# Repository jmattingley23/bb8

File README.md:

# bb8
full size sci-fi ball robot

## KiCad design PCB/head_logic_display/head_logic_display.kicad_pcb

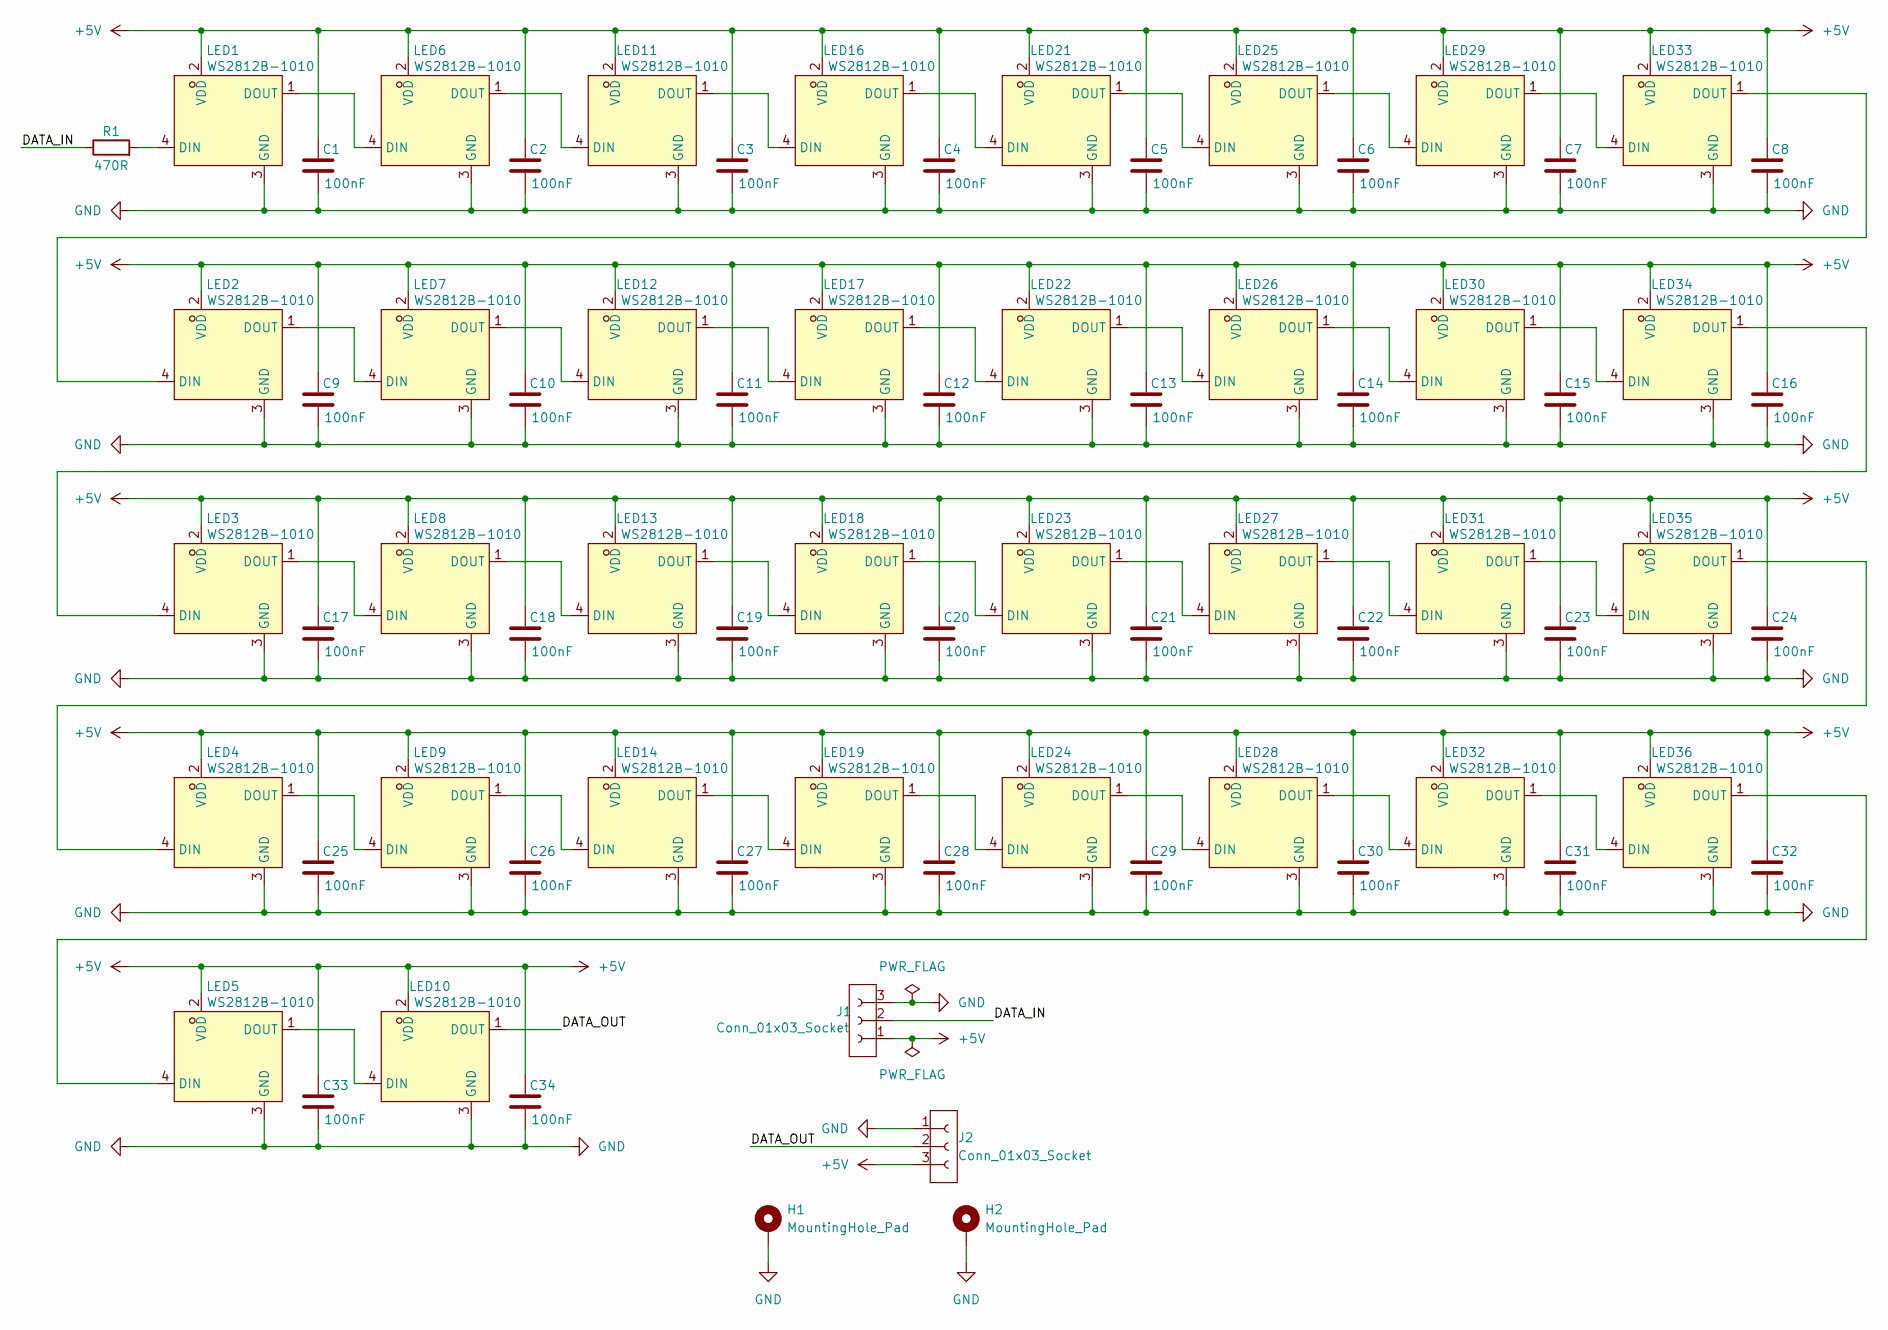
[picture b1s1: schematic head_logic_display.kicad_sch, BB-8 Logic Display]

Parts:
C1, C2, C3, C4, C5, C6, C7, C8, C9, C10, C11, C12, C13, C14, C15, C16, C17, C18, C19, C20, C21, C22, C23, C24, C25, C26, C27, C28, C29, C30, C31, C32, C33, C34: 100nF; C_0402_1005Metric; LCSC Part C307331
H1, H2: MountingHole_Pad; MountingHole_2.5mm_Pad_Via
J1, J2: Conn_01x03_Socket; JST_XH_S3B-XH-A-1_1x03_P2.50mm_Horizontal
LED1, LED2, LED3, LED4, LED5, LED6, LED7, LED8, LED9, LED10, LED11, LED12, LED13, LED14, LED16, LED17, LED18, LED19, LED21, LED22, LED23, LED24, LED25, LED26, LED27, LED28, LED29, LED30, LED31, LED32, LED33, LED34, LED35, LED36: WS2812B-1010; LED-SMD_4P-L1.0-W1.0-TL_XL-1010RGBC-WS2812B; LCSC Part C5349953
R1: 470R; R_0603_1608Metric; LCSC Part C23182

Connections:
+5V: C1.1, C2.1, C3.1, C4.1, C5.1, C6.1, C7.1, C8.1, C9.1, C10.1, C11.1, C12.1, C13.1, C14.1, C15.1, C16.1, C17.1, C18.1, C19.1, C20.1, C21.1, C22.1, C23.1, C24.1, C25.1, C26.1, C27.1, C28.1, C29.1, C30.1, C31.1, C32.1, C33.1, C34.1, J1.1, J2.3, LED1.2 (VDD), LED2.2 (VDD), LED3.2 (VDD), LED4.2 (VDD), LED5.2 (VDD), LED6.2 (VDD), LED7.2 (VDD), LED8.2 (VDD), LED9.2 (VDD), LED10.2 (VDD), LED11.2 (VDD), LED12.2 (VDD), LED13.2 (VDD), LED14.2 (VDD), LED16.2 (VDD), LED17.2 (VDD), LED18.2 (VDD), LED19.2 (VDD), LED21.2 (VDD), LED22.2 (VDD), LED23.2 (VDD), LED24.2 (VDD), LED25.2 (VDD), LED26.2 (VDD), LED27.2 (VDD), LED28.2 (VDD), LED29.2 (VDD), LED30.2 (VDD), LED31.2 (VDD), LED32.2 (VDD), LED33.2 (VDD), LED34.2 (VDD), LED35.2 (VDD), LED36.2 (VDD)
/DATA_IN: J1.2, R1.1
/DATA_OUT: J2.2, LED10.1 (DOUT)
GND: C1.2, C2.2, C3.2, C4.2, C5.2, C6.2, C7.2, C8.2, C9.2, C10.2, C11.2, C12.2, C13.2, C14.2, C15.2, C16.2, C17.2, C18.2, C19.2, C20.2, C21.2, C22.2, C23.2, C24.2, C25.2, C26.2, C27.2, C28.2, C29.2, C30.2, C31.2, C32.2, C33.2, C34.2, H1.1, H2.1, J1.3, J2.1, LED1.3 (GND), LED2.3 (GND), LED3.3 (GND), LED4.3 (GND), LED5.3 (GND), LED6.3 (GND), LED7.3 (GND), LED8.3 (GND), LED9.3 (GND), LED10.3 (GND), LED11.3 (GND), LED12.3 (GND), LED13.3 (GND), LED14.3 (GND), LED16.3 (GND), LED17.3 (GND), LED18.3 (GND), LED19.3 (GND), LED21.3 (GND), LED22.3 (GND), LED23.3 (GND), LED24.3 (GND), LED25.3 (GND), LED26.3 (GND), LED27.3 (GND), LED28.3 (GND), LED29.3 (GND), LED30.3 (GND), LED31.3 (GND), LED32.3 (GND), LED33.3 (GND), LED34.3 (GND), LED35.3 (GND), LED36.3 (GND)
unnamed: LED1.4 (DIN), R1.2
unnamed: LED1.1 (DOUT), LED6.4 (DIN)
unnamed: LED2.4 (DIN), LED33.1 (DOUT)
unnamed: LED2.1 (DOUT), LED7.4 (DIN)
unnamed: LED3.4 (DIN), LED34.1 (DOUT)
unnamed: LED3.1 (DOUT), LED8.4 (DIN)
unnamed: LED4.1 (DOUT), LED9.4 (DIN)
unnamed: LED5.1 (DOUT), LED10.4 (DIN)
unnamed: LED6.1 (DOUT), LED11.4 (DIN)
unnamed: LED11.1 (DOUT), LED16.4 (DIN)
unnamed: LED7.1 (DOUT), LED12.4 (DIN)
unnamed: LED12.1 (DOUT), LED17.4 (DIN)
unnamed: LED8.1 (DOUT), LED13.4 (DIN)
unnamed: LED13.1 (DOUT), LED18.4 (DIN)
unnamed: LED9.1 (DOUT), LED14.4 (DIN)
unnamed: LED14.1 (DOUT), LED19.4 (DIN)
unnamed: LED16.1 (DOUT), LED21.4 (DIN)
unnamed: LED17.1 (DOUT), LED22.4 (DIN)
unnamed: LED18.1 (DOUT), LED23.4 (DIN)
unnamed: LED19.1 (DOUT), LED24.4 (DIN)
unnamed: LED21.1 (DOUT), LED25.4 (DIN)
unnamed: LED22.1 (DOUT), LED26.4 (DIN)
unnamed: LED23.1 (DOUT), LED27.4 (DIN)
unnamed: LED24.1 (DOUT), LED28.4 (DIN)
unnamed: LED25.1 (DOUT), LED29.4 (DIN)
unnamed: LED26.1 (DOUT), LED30.4 (DIN)
unnamed: LED27.1 (DOUT), LED31.4 (DIN)
unnamed: LED28.1 (DOUT), LED32.4 (DIN)
unnamed: LED29.1 (DOUT), LED33.4 (DIN)
unnamed: LED30.1 (DOUT), LED34.4 (DIN)
unnamed: LED31.1 (DOUT), LED35.4 (DIN)
unnamed: LED32.1 (DOUT), LED36.4 (DIN)
unnamed: LED4.4 (DIN), LED35.1 (DOUT)
unnamed: LED5.4 (DIN), LED36.1 (DOUT)

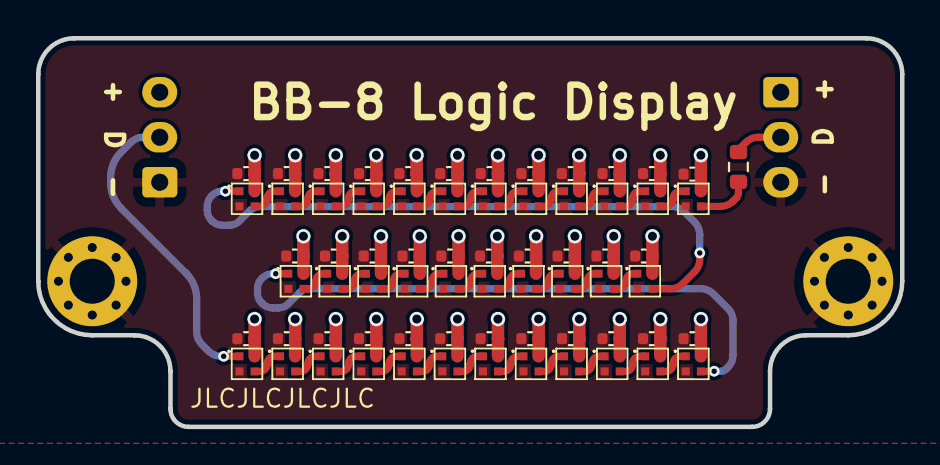
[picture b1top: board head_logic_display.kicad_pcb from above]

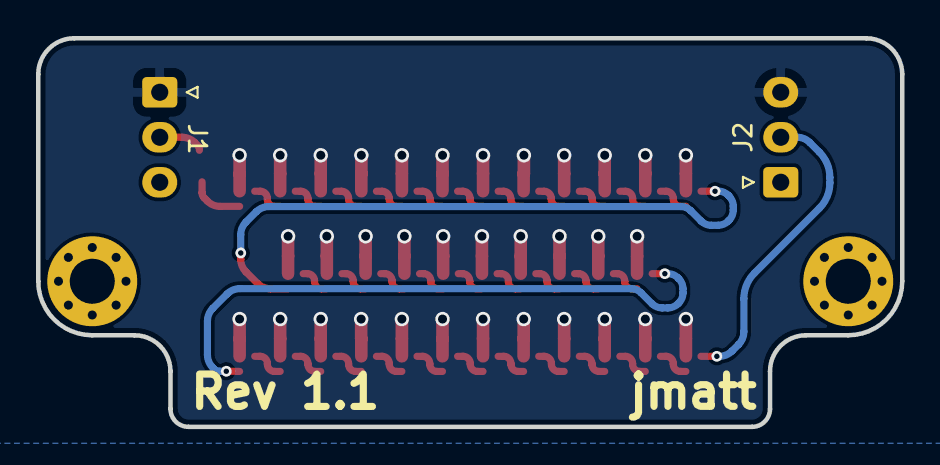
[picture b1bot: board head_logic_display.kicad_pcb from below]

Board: 2 copper layers, 48.0 x 21.6 mm, 73 parts (2 on the bottom side), 38 nets.

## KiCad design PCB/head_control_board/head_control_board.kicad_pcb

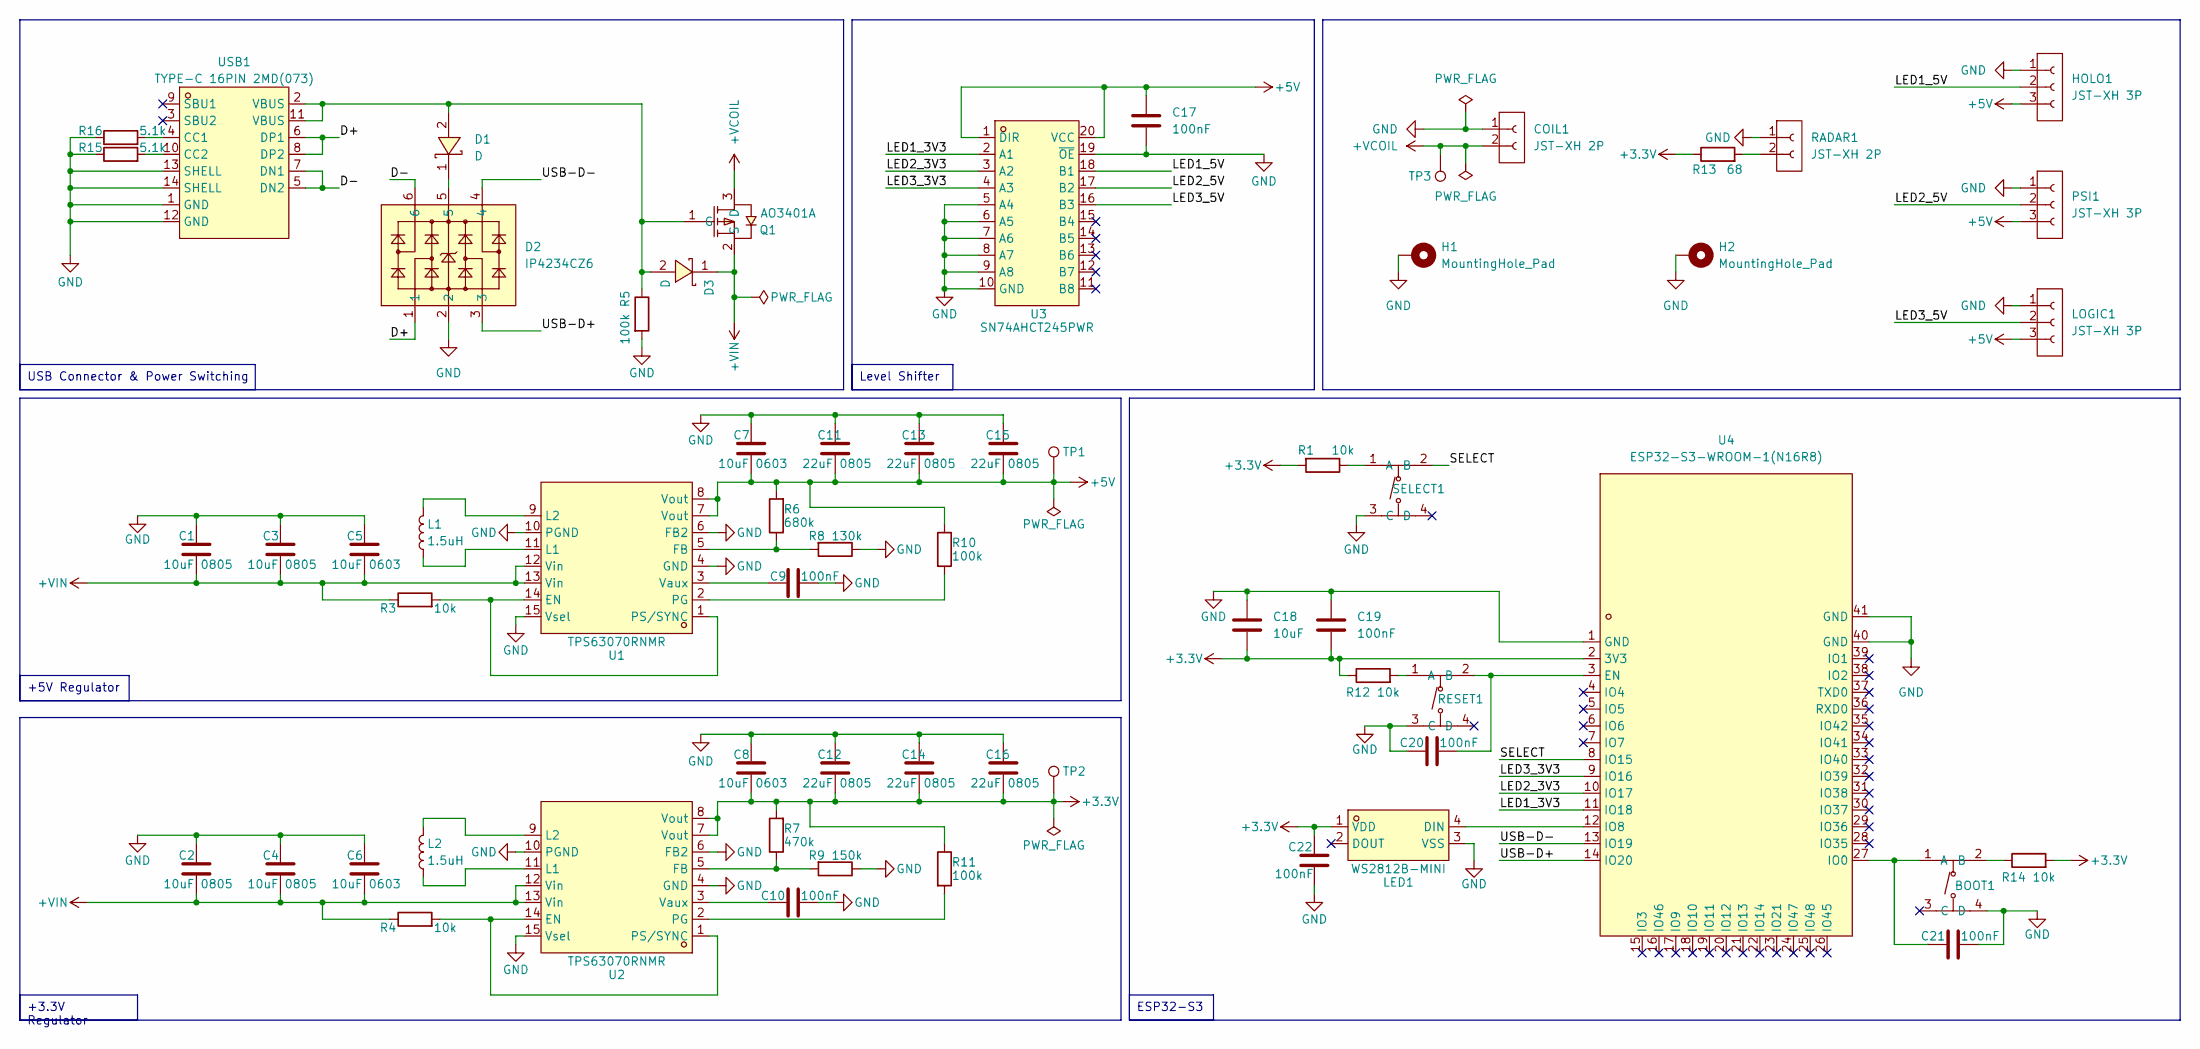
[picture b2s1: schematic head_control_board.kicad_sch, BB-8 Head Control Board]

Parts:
BOOT1: TS-1187A-B-A-B; SW-SMD_4P-L5.2-W5.2-P3.70-LS6.4
C1, C2, C3, C4: 10uF 0805; C_0805_2012Metric; LCSC Part C440198
C5, C6, C7, C8: 10uF 0603; C_0603_1608Metric; LCSC Part C96446
C9, C10, C17, C19, C20, C21, C22: 100nF; C_0402_1005Metric; LCSC Part C307331
C11, C12, C13, C14, C15, C16: 22uF 0805; C_0805_2012Metric; LCSC Part C45783
C18: 10uF; C_0805_2012Metric; LCSC Part C440198
COIL1: JST-XH 2P; JST_XH_S2B-XH-A-1_1x02_P2.50mm_Horizontal
D1, D3: D; SMA_L4.3-W2.6-LS5.2-RD; LCSC Part C8678
D2: IP4234CZ6; SOT-457_L2.9-W1.5-P0.95-LS2.8-BL; LCSC Part C455086
H1, H2: MountingHole_Pad; MountingHole_2.5mm_Pad_Via
HOLO1: JST-XH 3P; JST_XH_S3B-XH-A-1_1x03_P2.50mm_Horizontal
L1, L2: 1.5uH; IND-SMD_L7.0-W6.6; LCSC Part C408444
LED1: WS2812B-MINI; LED-SMD_4P-L3.5-W3.5-TL_WS2812B; LCSC Part C527089
LOGIC1: JST-XH 3P; JST_XH_S3B-XH-A-1_1x03_P2.50mm_Horizontal
PSI1: JST-XH 3P; JST_XH_S3B-XH-A-1_1x03_P2.50mm_Horizontal
Q1: AO3401A; SOT-23_L2.9-W1.3-P1.90-LS2.4-BR; LCSC Part C15127
R1, R3, R4, R12, R14: 10k; R_0402_1005Metric; LCSC Part C25744
R5, R10, R11: 100k; R_0402_1005Metric; LCSC Part C25741
R6: 680k; R_0603_1608Metric; LCSC Part C25822
R7: 470k; R_0603_1608Metric; LCSC Part C23178
R8: 130k; R_0603_1608Metric; LCSC Part C22795
R9: 150k; R_0603_1608Metric; LCSC Part C22807
R13: 68; R_Axial_DIN0207_L6.3mm_D2.5mm_P7.62mm_Horizontal
R15, R16: 5.1k; R_0805_2012Metric; LCSC Part C27834
RADAR1: JST-XH 2P; JST_XH_S2B-XH-A-1_1x02_P2.50mm_Horizontal
RESET1: TS-1187A-B-A-B; SW-SMD_4P-L5.2-W5.2-P3.70-LS6.4
SELECT1: TS-1187A-B-A-B; SW-SMD_4P-L5.2-W5.2-P3.70-LS6.4
TP1, TP2, TP3: TestPoint; TestPoint_Pad_D2.0mm
U1, U2: TPS63070RNMR; VQFN-HR-15_L3.0-W2.5-P0.50-BL_TPS63070RNMR; LCSC Part C109322
U3: SN74AHCT245PWR; TSSOP-20_L6.5-W4.4-P0.65-LS6.4-BL; LCSC Part C10910
U4: ESP32-S3-WROOM-1(N16R8); WIRELM-SMD_ESP32-S3-WROOM-1; LCSC Part C2913202
USB1: TYPE-C 16PIN 2MD(073); USB-C-SMD_TYPE-C-6PIN-2MD-073; LCSC Part C2765186

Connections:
+3.3V: C8.2, C12.2, C14.2, C16.2, C18.2, C19.2, C22.1, LED1.1 (VDD), R1.2, R7.2, R11.1, R12.1, R13.1, R14.2, TP2.1, U2.7 (Vout), U2.8 (Vout), U4.2 (3V3)
+5V: C7.2, C11.2, C13.2, C15.2, C17.2, HOLO1.3, LOGIC1.3, PSI1.3, R6.2, R10.1, TP1.1, U1.7 (Vout), U1.8 (Vout), U3.1 (DIR), U3.20 (VCC)
+VCOIL: COIL1.2, Q1.3 (D), TP3.1
+VIN: C1.2, C2.2, C3.2, C4.2, C5.2, C6.2, D3.1, Q1.2 (S), R3.1, R4.1, U1.12 (Vin), U1.13 (Vin), U2.12 (Vin), U2.13 (Vin)
/D+: D2.1, USB1.6 (DP1), USB1.8 (DP2)
/D-: D2.6, USB1.5 (DN2), USB1.7 (DN1)
/LED1_3V3: U3.2 (A1), U4.11 (IO18)
/LED1_5V: HOLO1.2, U3.18 (B1)
/LED2_3V3: U3.3 (A2), U4.10 (IO17)
/LED2_5V: PSI1.2, U3.17 (B2)
/LED3_3V3: U3.4 (A3), U4.9 (IO16)
/LED3_5V: LOGIC1.2, U3.16 (B3)
/SELECT: SELECT1.2 (B), U4.8 (IO15)
/USB-D+: D2.3, U4.14 (IO20)
/USB-D-: D2.4, U4.13 (IO19)
GND: BOOT1.4 (D), C1.1, C2.1, C3.1, C4.1, C5.1, C6.1, C7.1, C8.1, C9.2, C10.2, C11.1, C12.1, C13.1, C14.1, C15.1, C16.1, C17.1, C18.1, C19.1, C20.1, C21.2, C22.2, COIL1.1, D2.2, H1.1, H2.1, HOLO1.1, LED1.3 (VSS), LOGIC1.1, PSI1.1, R5.2, R8.1, R9.1, R15.1, R16.1, RADAR1.1, RESET1.3 (C), SELECT1.3 (C), U1.4 (GND), U1.6 (FB2), U1.10 (PGND), U1.15 (Vsel), U2.4 (GND), U2.6 (FB2), U2.10 (PGND), U2.15 (Vsel), U3.5 (A4), U3.6 (A5), U3.7 (A6), U3.8 (A7), U3.9 (A8), U3.10 (GND), U3.19 (~OE), U4.1 (GND), U4.40 (GND), U4.41 (GND), USB1.1 (GND), USB1.12 (GND), USB1.13 (SHELL), USB1.14 (SHELL)
unnamed: BOOT1.1 (A), C21.1, U4.27 (IO0)
unnamed: BOOT1.2 (B), R14.1
unnamed: D1.1, D2.5
unnamed: LED1.4 (DIN), U4.12 (IO8)
unnamed: D1.2, D3.2, Q1.1 (G), R5.1, USB1.2 (VBUS), USB1.11 (VBUS)
unnamed: R13.2, RADAR1.2
unnamed: R12.2, RESET1.1 (A)
unnamed: C20.2, RESET1.2 (B), U4.3 (EN)
unnamed: R1.1, SELECT1.1 (A)
unnamed: R3.2, U1.1 (PS/SYNC), U1.14 (EN)
unnamed: R6.1, R8.2, U1.5 (FB)
unnamed: L1.1, U1.11 (L1)
unnamed: L1.2, U1.9 (L2)
unnamed: R10.2, U1.2 (PG)
unnamed: C9.1, U1.3 (Vaux)
unnamed: R4.2, U2.1 (PS/SYNC), U2.14 (EN)
unnamed: R7.1, R9.2, U2.5 (FB)
unnamed: L2.1, U2.11 (L1)
unnamed: L2.2, U2.9 (L2)
unnamed: R11.2, U2.2 (PG)
unnamed: C10.1, U2.3 (Vaux)
unnamed: R16.2, USB1.4 (CC1)
unnamed: R15.2, USB1.10 (CC2)

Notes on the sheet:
USB Connector & Power Switching
+5V Regulator
+3.3V Regulator
ESP32-S3
Level Shifter

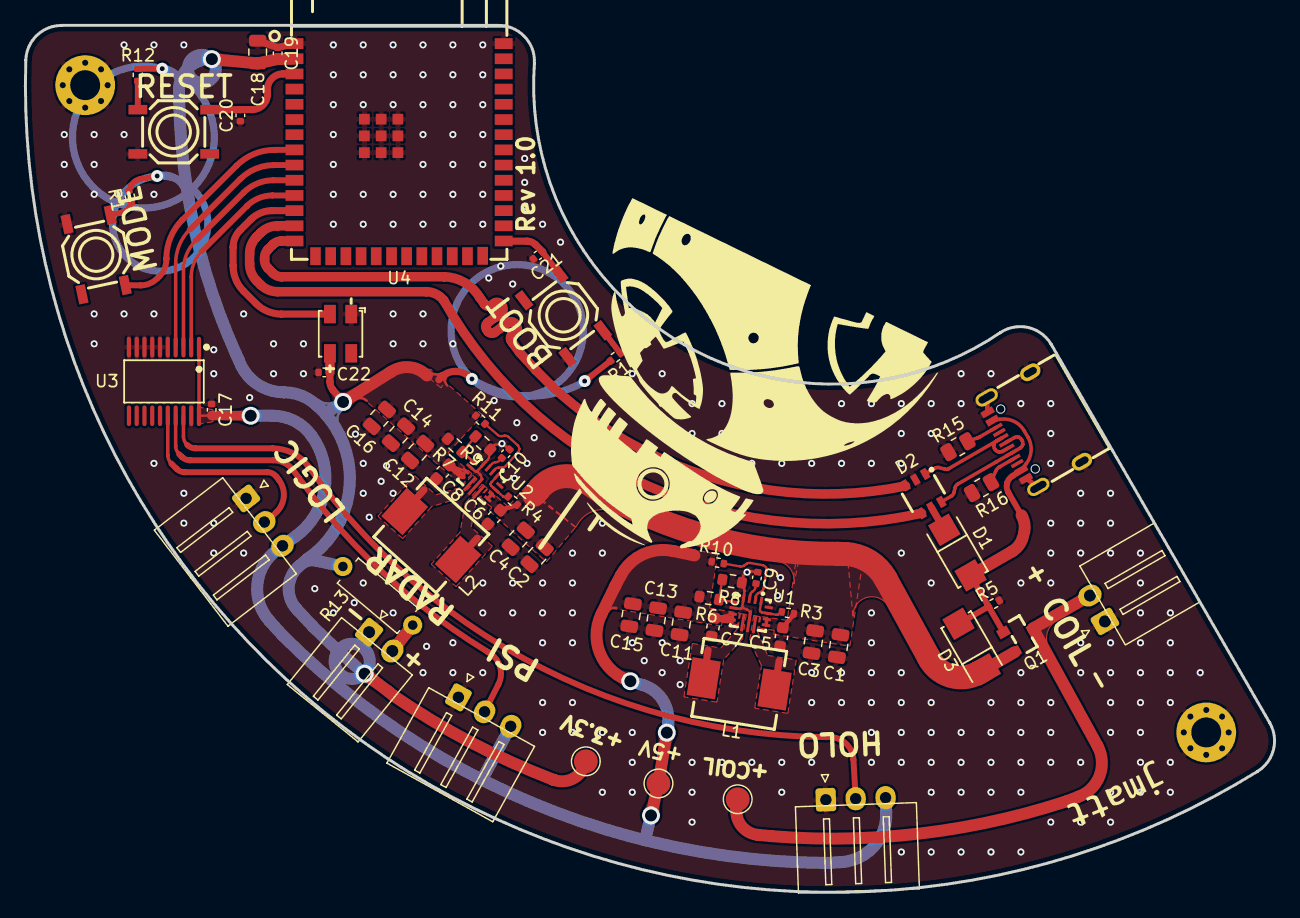
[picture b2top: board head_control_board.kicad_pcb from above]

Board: 2 copper layers, 104.5 x 72.5 mm, 62 parts (0 on the bottom side), 39 nets.

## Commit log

2024-04-02 Autocommit from 2024-04-02 14:33:08
2024-04-02 Add .gitignore
2024-04-02 Autocommit from 2024-04-02 14:34:10
2024-04-02 Autocommit from 2024-04-02 14:34:27
2024-04-05 Autocommit from 2024-04-04 22:49:25
2024-04-06 Autocommit from 2024-04-05 18:19:23
2024-04-06 Autocommit from 2024-04-05 18:20:54
2024-04-07 Autocommit from 2024-04-06 21:12:11
2024-04-09 Autocommit from 2024-04-08 18:04:38
2024-04-12 Autocommit from 2024-04-11 20:23:44
2024-04-15 Autocommit from 2024-04-15 14:13:32
2024-04-21 Autocommit from 2024-04-20 21:06:19
2024-05-04 Autocommit from 2024-05-03 19:05:06
2024-05-21 Autocommit from 2024-05-20 19:20:46
2024-05-25 Autocommit from 2024-05-25 00:29:09
2024-06-18 Autocommit from 2024-06-18 13:26:40
2024-08-05 Autocommit from 2024-08-04 19:00:06
2024-08-05 Autocommit from 2024-08-04 23:30:22
2024-08-08 Autocommit from 2024-08-07 21:51:36
2024-08-09 Autocommit from 2024-08-08 23:26:05
2024-08-10 Autocommit from 2024-08-09 19:57:30
2024-08-10 Autocommit from 2024-08-09 20:25:35
2024-08-10 Autocommit from 2024-08-09 20:27:10
2024-08-10 Autocommit from 2024-08-10 13:28:44
2024-08-10 Autocommit from 2024-08-10 14:23:59
2024-08-11 Autocommit from 2024-08-10 18:08:53
2024-08-22 Add head_logic_display PCB schematic
2024-08-24 CAD update
2024-08-24 Finish component placement
2024-08-24 Finish board layout
2024-08-31 5V regulator
2024-08-31 Add MCU
2024-08-31 Remove .lck file
2024-08-31 remove backups dip diirectory
2024-09-01 Finish first pass of schematic
2024-09-05 Start caster wheel and magnet mount
2024-09-07 Finsh head carriage master sketch
2024-09-07 Add magnet holder
2024-09-09 Finish head caster assembly
2024-09-09 Add connector pin labels
2024-09-11 Finish lower carriage leg and hub
2024-09-13 Finish upper carriage hub
2024-09-14 Finish head carriage (hub version)
2024-09-14 Add lightweight set-screw upper carriage hub
2024-09-14 Update tab length on lower carriage leg dovetails
2024-09-16 Shorten caster fork; adjust legs accordingly
2024-09-16 Start magnet mount revisions
2024-09-17 Finish lightweight magnet mount; move to 1/4in magnets
2024-09-20 Add receiver pcb mount and cover
2024-09-20 Remove old receiver pcb cover
2024-09-21 Finish receiver coil mount
2024-09-22 Update schematic and route usb
2024-09-22 Finish USB differential routing
2024-09-22 Fillet tracks and update silkscreen
2024-09-22 First pass on voltage regulators
2024-09-24 Finish signal routing
2024-09-26 Finish power routing
2024-09-26 Finish GND planes
2024-09-26 Add via stitching
2024-09-27 Start passive component selection
2024-09-27 Finish component selection
2024-09-27 Component cost optimization
2024-09-28 Rev 1.0 boards ordered
2024-10-24 Add head sendcutsend .dxfs
2024-10-24 Improve diffusion and smd clearance on logic lens housings
2024-11-10 platformio project setup & initial head code
2024-11-10 Add brightness control
2024-11-10 Add PSI and holoprojector functionality
2024-11-11 Fix rear logic lens mount angle
2024-11-13 Increase dome rigng countersink
2024-12-22 Fix logic lens led rotation
2025-01-18 Add front logic lens sanding jig
2025-01-19 Loosen sanding jig print tolerance
2025-01-19 Add reference to controller repo
2025-01-25 Update sanding jig
2025-01-25 Rollback to SW 2024
